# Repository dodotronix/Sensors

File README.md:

# SENSORS 
This is my library of sensors, with some test codes, for fast usage. I used them
in my last project "Robot Claire".

## ST VL6180X

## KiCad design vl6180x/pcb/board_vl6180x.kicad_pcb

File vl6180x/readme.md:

## VL6180X - IR Proximity sensor

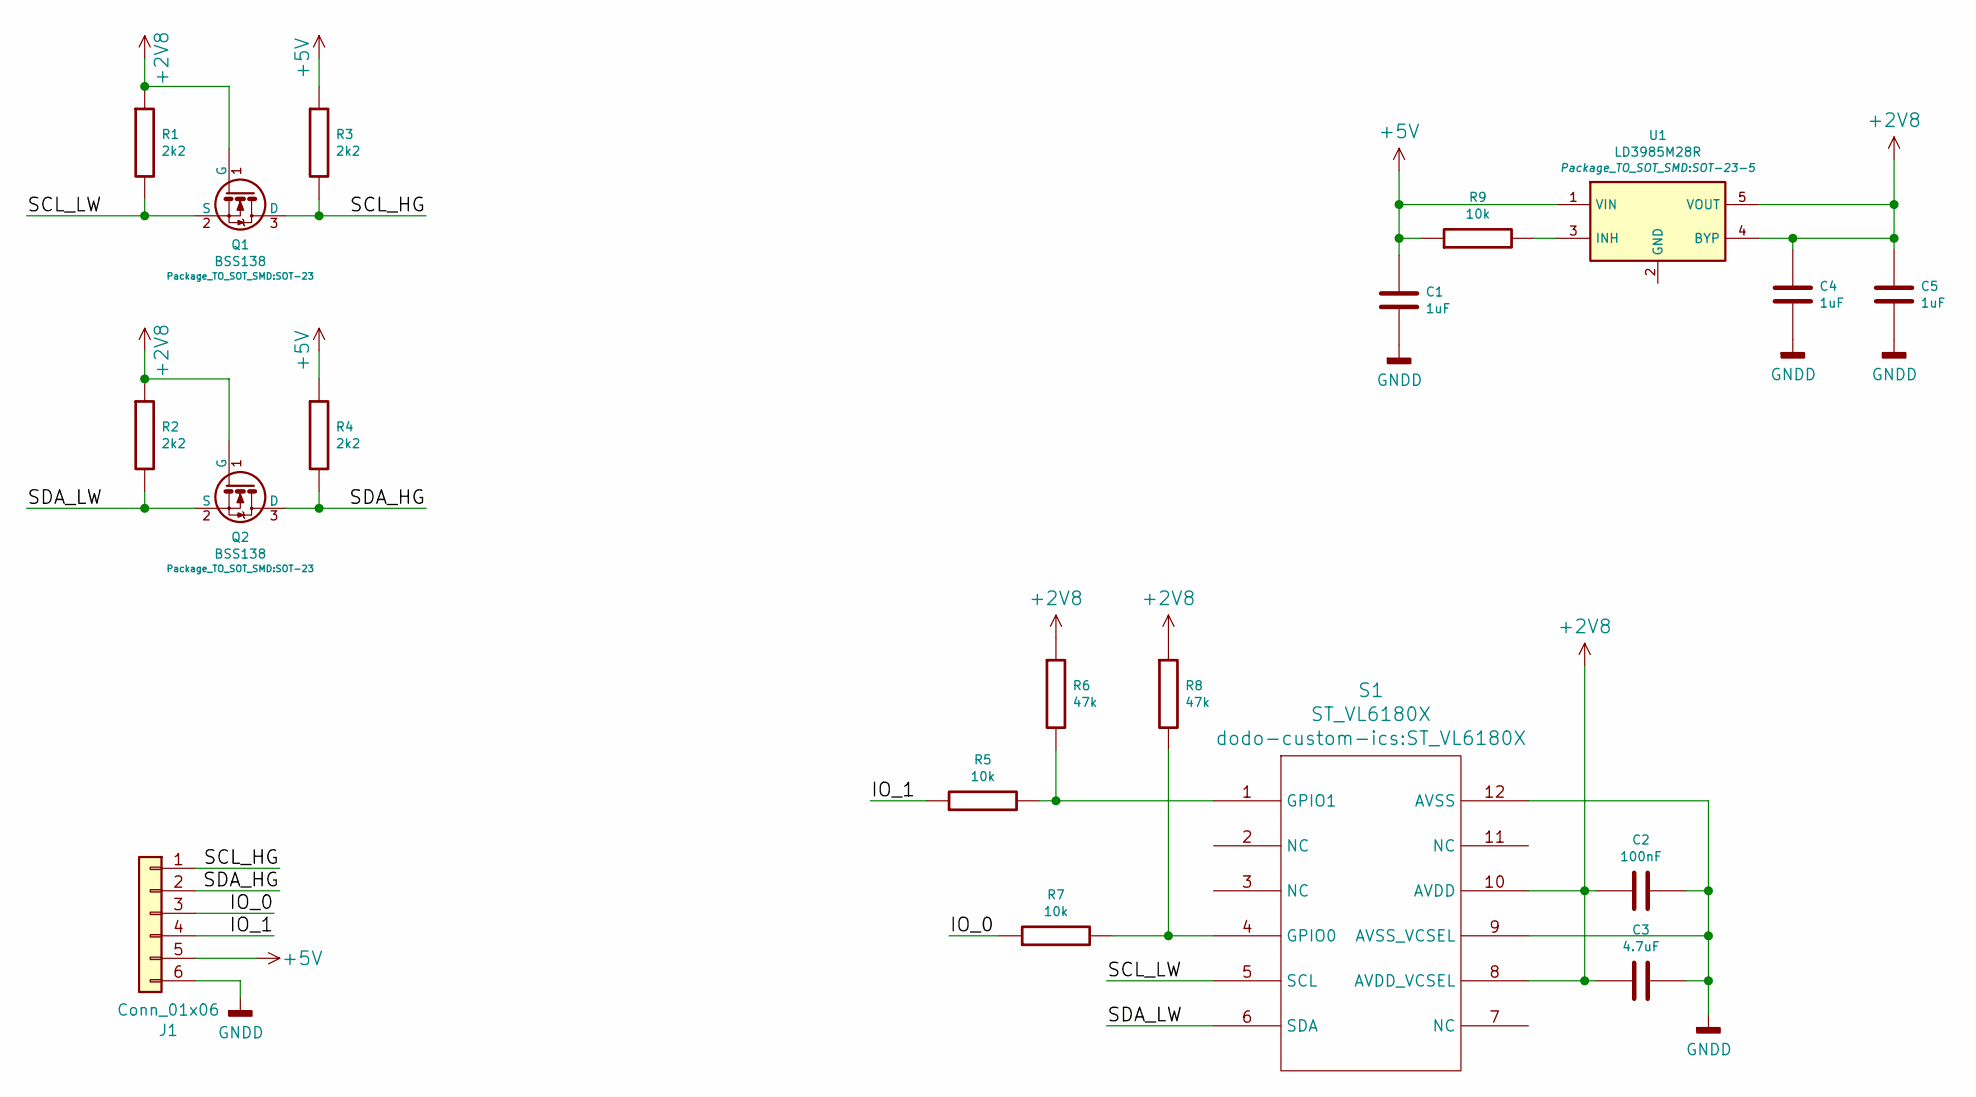
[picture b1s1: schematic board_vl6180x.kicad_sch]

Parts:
C1, C4, C5: 1uF; R_0603_1608Metric
C2: 100nF; R_0603_1608Metric
C3: 4.7uF; R_0603_1608Metric
J1: Conn_01x06; PinHeader_1x06_P2.54mm_Horizontal
Q1, Q2: BSS138; SOT-23
R1, R2, R3, R4: 2k2; R_0603_1608Metric
R5, R7: 10k; R_0603_1608Metric
R6, R8: 47k; R_0603_1608Metric
R9: 10k; R_0805_2012Metric
S1: ST_VL6180X
U1: LD3985M28R; SOT-23-5

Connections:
+2V8: C2.1, C3.1, C4.1, C5.1, Q1.1 (G), Q2.1 (G), R1.1, R2.1, R6.1, R8.1, S1.8 (AVDD_VCSEL), S1.10 (AVDD), U1.4 (BYP), U1.5 (VOUT)
+5V: C1.1, J1.5, R3.1, R4.1, R9.1, U1.1 (VIN)
/IO_0: J1.3, R7.1
/IO_1: J1.4, R5.1
/SCL_HG: J1.1, Q1.3 (D), R3.2
/SCL_LW: Q1.2 (S), R1.2, S1.5 (SCL)
/SDA_HG: J1.2, Q2.3 (D), R4.2
/SDA_LW: Q2.2 (S), R2.2, S1.6 (SDA)
GNDD: C1.2, C2.2, C3.2, C4.2, C5.2, J1.6, S1.9 (AVSS_VCSEL), S1.12 (AVSS)
unnamed: R5.2, R6.2, S1.1 (GPIO1)
unnamed: R7.2, R8.2, S1.4 (GPIO0)
unnamed: R9.2, U1.3 (INH)

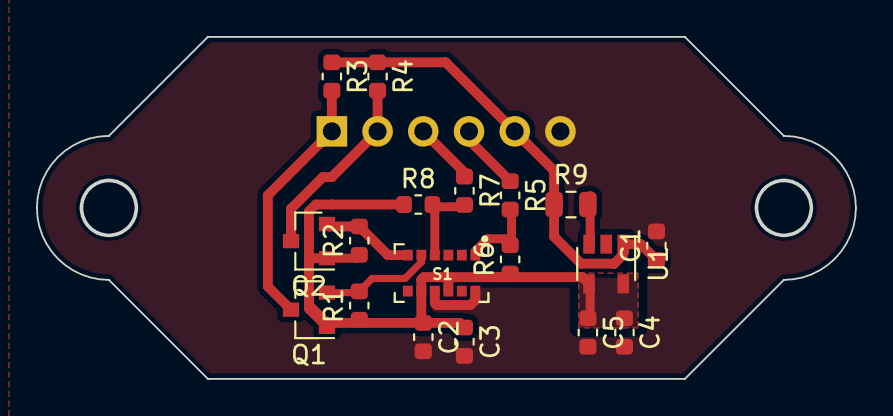
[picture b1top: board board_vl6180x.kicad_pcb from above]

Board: 2 copper layers, 45.5 x 19.0 mm, 19 parts (1 on the bottom side), 12 nets.

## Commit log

2018-06-24 new project readme
2018-06-24 src for RPi platform
2018-06-24 new readme (hmc5883l)
2018-06-24 kicad pcb layout
2018-06-24 new readme (vl6180x)
2020-09-30 rerouting tracks and utilization of my own libraries
2020-09-30 sensor kicad model pictures
2020-09-30 additional photos
2020-09-30 text change
